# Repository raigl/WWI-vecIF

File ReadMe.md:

# Whirlwind I Vector Graphics Interface

For showing a Whirlwind programme's output, a small hardware
generates vector strokes on X/Y/Z oszilloskopes
and allows to attach light guns.
Guy Fedorkow's WWI simulator ([https://github.com/gfedorkow/Whirlwind-Instruction-Simulator]) running on a Raspberry (B+) 
can drive the interface and run some original WWI programmes.

## Directories

<dl>
<dt> CAD   <dd> 3D Light gun case 3D files 
<dt> DOC   <dd> Documentation (own and collected)  
<dt> KiCad <dd> Schematics and PCB drawings
<dt> src   <dd> Python and Arduino source
</dl>

## Versions

0.3     Working prototype

1.0     Redesigned

## Basics

The interface allows to draw (short) vectors for two channels
on an analog x/y/z display, e.g. an oszilloscope.
Points are drawn as zero-length vectors.

The D/A converter used has an internal reference of 2.048V, 12 bits
resolution and produces 0..2.047V in steps of 1/4096. 
WWI uses 10 bits plus sign, i.e. +/- 1023.
Thus the coordinate unit corresponds to 1mV internally.
The output state amplifies by 3 (and shifts to zero base), 
thus supplies +/- 3V and 3mV per unit. 

Drawing a vector is done by setting two integrators to the start point,
then provide a speed and start the integrators for 50µs,
which at the same time provides a strobe for the z axis.
With maximum speed (-1023 or +1023, i.e. 0 or 2.047V), the movement is 1/8 of the full coordinate range -1.0 .. +1.0,
i.e. 256 coordinate units or 250mV. 
Thus coordinate differences must be multiplied by 4 to set the speed. 
Longer vectors must be drawn as segments.

The display should be setup such that increasing both coordinates
moves the point right and up.

Character display is not done by hardware as in WWI,
but by software as a chain of segments;
this requires a precise setup of the mid voltage
to 1.023V; otherwise the characters are blurred.

Vector drawing was inspried by the Vectrex gaming console.
Original WWI hardware used a more elaborate method:
A fixed ramp generator (for each coordinate) was multiplied by
the vector delta coordinate provided. 
The advantage is that the end points and do not depend on the precision of the integration capacitor.
Also the strobe start and end could be slightly before and after the end of the ramp, 
ensuring that a chain of vectors has no gaps.

## Displays
 
To display the vectors, the display device must have analog inputs for X/Y mode
and a (digital) Z input for intensitiy modulation.

To better mimic the original, the vector interface board provides
a display bus connector to be used with one or more display tap boards,
which are located directly near a display.

Each display tap board has two switches to select one or both intensification
lines (the original had 15). 

A light gun (light pen) for interactive mode can be connected to a display tap board
and configured for one of two light gun inputs.

Four more switches with lamps (LEDs) can be set by either the user or WWI 
programme.

Displays could in particular be oszilloscopes with a trace blanking
or unblanking input (Z-input).
The amplitude of the X and Y signals is &plusmn;3V which can be attenuated
with a potentiometer on the board.
Z output is 5V (TTL) digital output with 50µs active pulses.
Polarity can be configured on the tap board.

Displays that work without modifications are:
- Grundig GO-40Z oszilloscope (with Z-option)
- Tektronix 1740A oszilloscope 
- Tektronix 611 storage display unit

The Tektronix 611 can be swiched to non-storage mode and is normally 
internally wired for +/- 1V sensitivity; 
thus the potentimeters on the tap board are required.

Several other oscilloscopes have a Z option, but often require
at least 20V to blank the trace.
For this cases, a variant of the tap board has provisions for a voltage converter
and corresponding output amplifier.
Some (e.g. Hameg) are designed for blanking small parts of the trace
only by a diode clamp for the coupling capacitor;
this diode has to be removed or reversed, otherwise the blanking would not work.
 
A Hameg HM512 was succesfully modified by reversing the diode and also
adding internally a small amplifier to obtain larger voltage swing
from the Z-input. 

## I²C Bus

The interface board has a connection to access the Rapi's (second) I²C bus,
shifted to 5V operation.

With upto eight PCF8574, each can drive 8 swiches and lamps.

Note that the WWI had no console, but was to a large extend controlled
by panel switches and lights.

## 5V only operation

The board can be driven by a 5V Arduino.
In this case, JP3 must be cut and changed.
The voltage stablizer U9 (LP 2950-3.3) must be used.
The 3.3V pins are then supplied with 5V.

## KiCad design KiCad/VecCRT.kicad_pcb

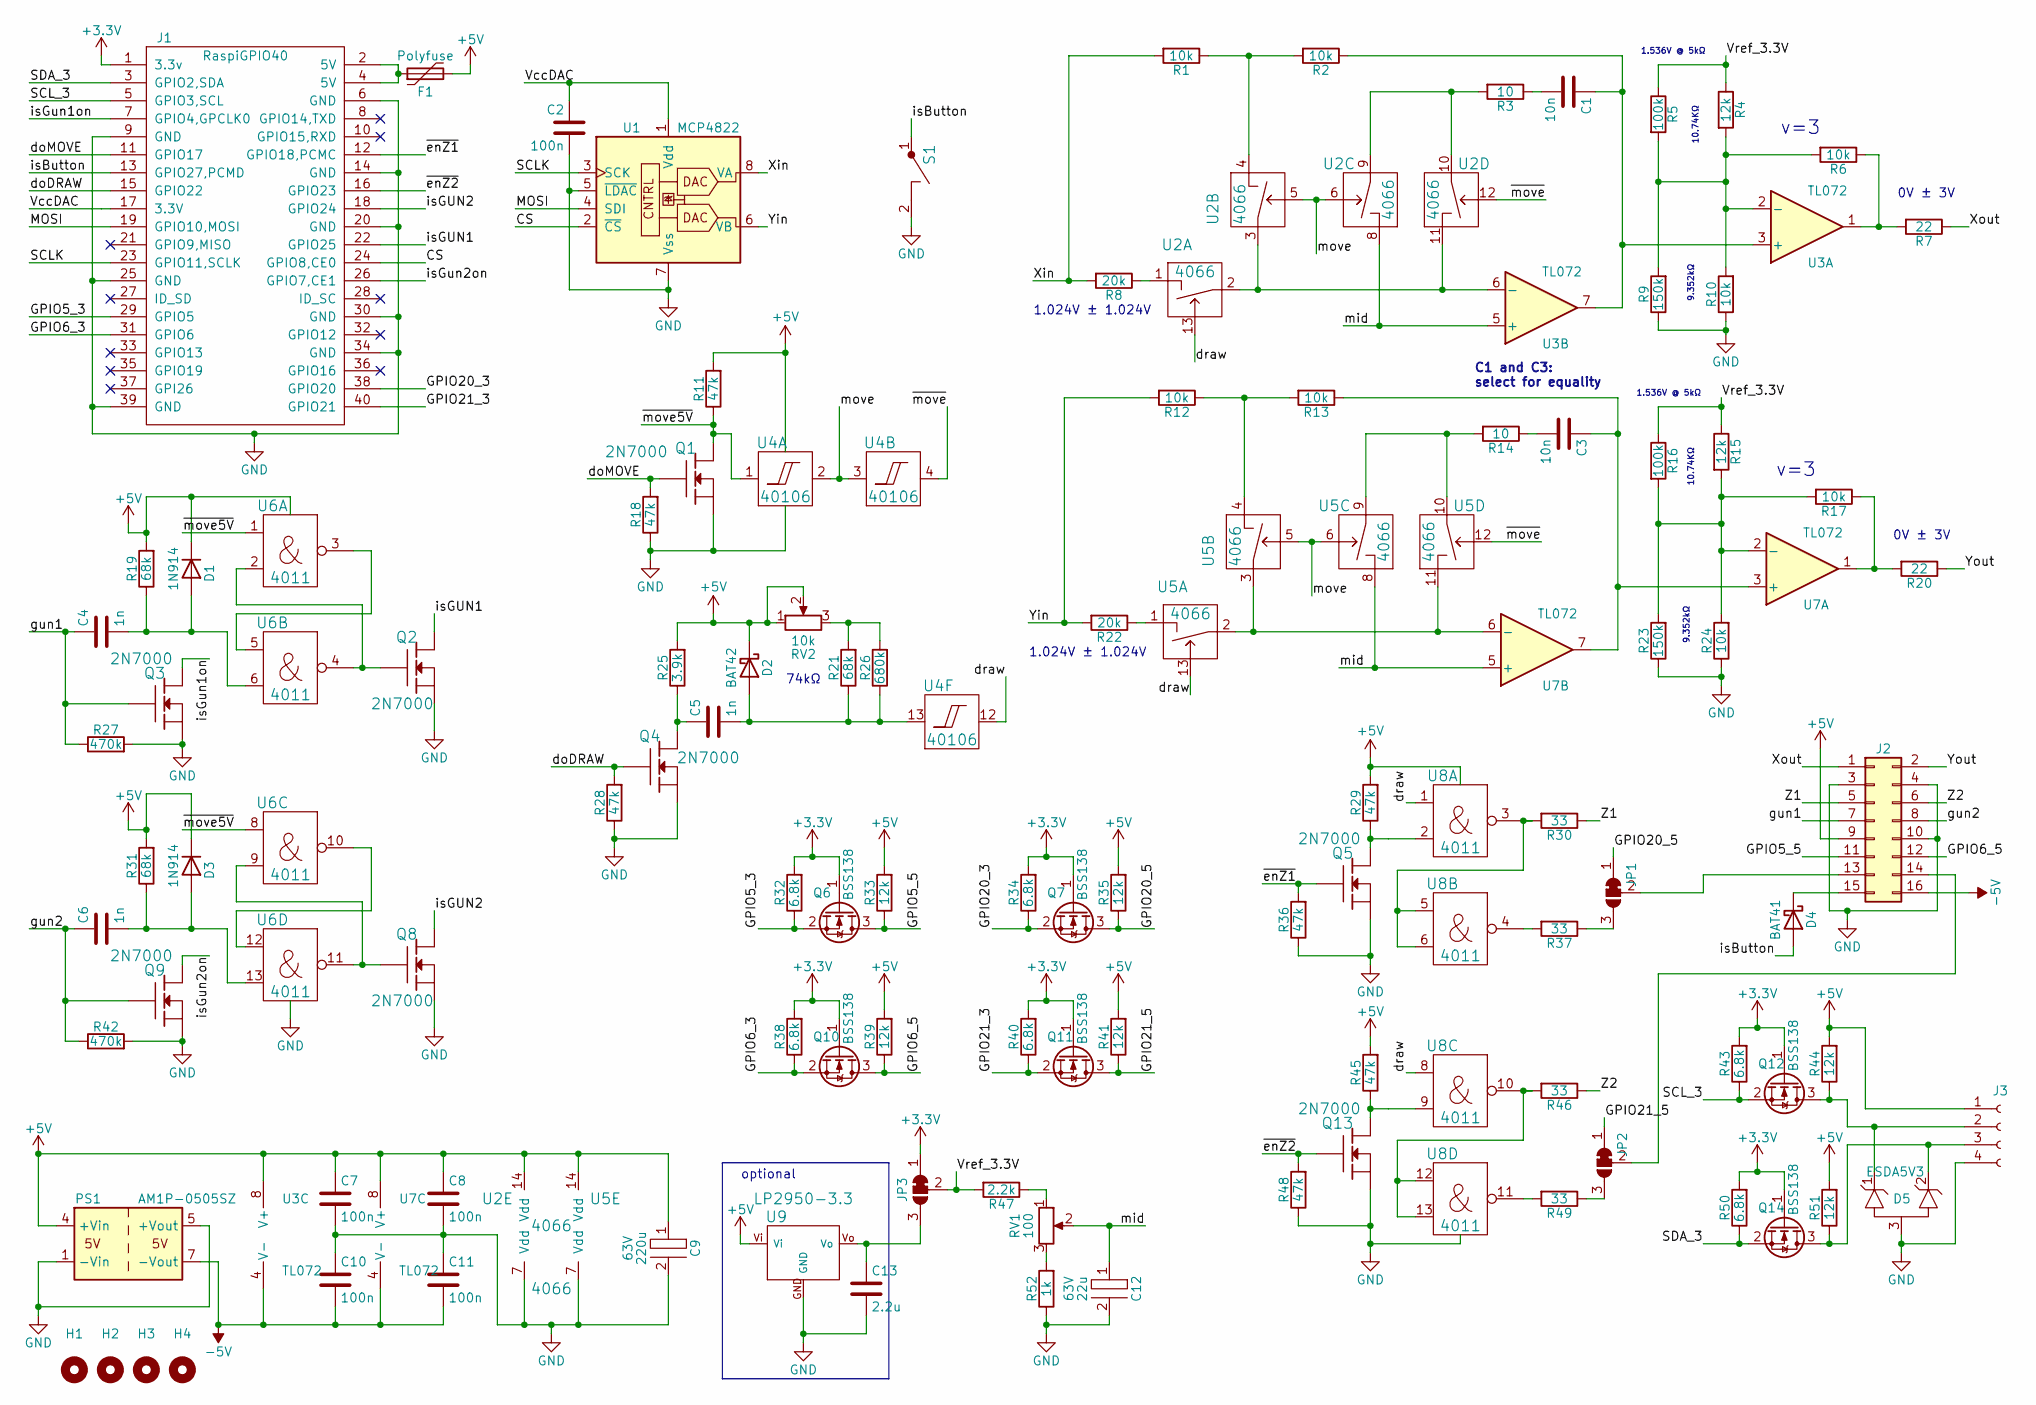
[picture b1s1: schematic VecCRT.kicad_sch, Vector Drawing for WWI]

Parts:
C1, C3: 10n; C2-2
C2, C7, C8, C10, C11: 100n; SM-1206B
C4, C5, C6: 1n; C2-2
C9: 220u; C2-7; Voltage 63V
C12: 22u; C2-7; Voltage 63V
C13: 2.2u; SM-1206B
D1, D3: 1N914; D_DO-35_SOD27_P7.62mm_Horizontal
D2: BAT42; D_DO-35_SOD27_P7.62mm_Horizontal
D4: BAT41; D_DO-35_SOD27_P7.62mm_Horizontal
D5: ESDA5V3; SOT-23_Handsoldering
F1: Polyfuse; Fuse_Bourns_MF-RG300
H1, H2, H3, H4: MountingHole; MountingHole_3.2mm_M3
J1: RaspiGPIO40; Wannenstecker_2x20_V
J2: Conn_02x08_Odd_Even; Wannenstecker_2x08_V
J3: Conn_01x04_Female; PSS_4
JP1, JP2: SolderJumper_3_Open; SolderJumper-3_P1.3mm_Bridged12_RoundedPad1.0x1.5mm
JP3: SolderJumper_3_Bridged12; SolderJumper-3_P1.3mm_Bridged12_RoundedPad1.0x1.5mm
PS1: AM1P-0505SZ; AM1P-SZ
Q1, Q2, Q3, Q4, Q5, Q8, Q9, Q13: 2N7000; FETsgd_inline
Q6, Q7, Q10, Q11, Q12, Q14: BSS138; SOT-23
R1, R2, R6, R10, R12, R13, R17, R24: 10k; R4-2
R3, R14: 10; R4-2
R4, R15: 12k; R4-2
R5, R16: 100k; R4-2
R7, R20: 22; R4-2
R8, R22: 20k; R4-2
R9, R23: 150k; R4-2
R11, R29, R45: 47k; R4-2
R18, R28, R36, R48: 47k; SM-1206B
R19, R21, R31: 68k; R4-2
R25: 3.9k; R4-2
R26: 680k; SM-1206B
R27, R42: 470k; SM-1206B
R30, R37, R46, R49: 33; R4-2
R32, R34, R38, R40, R43, R50: 6.8k; SM-1206B
R33, R35, R39, R41, R44, R51: 12k; SM-1206B
R47: 2.2k; R4-2
R52: 1k; R4-2
RV1: 100; Pot64y
RV2: 10k; Pot64y
S1: TASTER; Tast2mil
U1: MCP4822; DIP-8_300
U2, U5: 4066; DIP-14_W7.62mm_LongPads
U3, U7: TL072; DIP-8_300
U4: 40106; DIP-14_W7.62mm_LongPads
U6, U8: 4011; DIP-14_W7.62mm_LongPads
U9: LP2950-3.3; TO-92ViGNDVo

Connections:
+3.3V: J1.1 (3.3v), JP3.1 (A), Q6.1 (G), Q7.1 (G), Q10.1 (G), Q11.1 (G), Q12.1 (G), Q14.1 (G), R32.2, R34.2, R38.2, R40.2, R43.2, R50.2
+5V: C7.1, C8.1, C9.1, D1.1 (K), D2.1 (K), D3.1 (K), F1.2, J2.9, J3.1, PS1.4 (+Vin), R11.2, R19.2, R25.2, R29.2, R31.2, R33.2, R35.2, R39.2, R41.2, R44.2, R45.2, R51.2, RV2.1, RV2.2, U2.14 (Vdd), U3.8 (V+), U4.14, U5.14 (Vdd), U6.14 (VDD), U7.8 (V+), U8.14 (VDD), U9.Vi
-5V: C10.2, C11.2, J2.16, PS1.7 (-Vout), U3.4 (V-), U7.4 (V-)
/CS: J1.24 (GPIO8,CE0), U1.2 (~CS)
/GPIO5_3: J1.29 (GPIO5), Q6.2 (S), R32.1
/GPIO5_5: J2.11, Q6.3 (D), R33.1
/GPIO6_3: J1.31 (GPIO6), Q10.2 (S), R38.1
/GPIO6_5: J2.12, Q10.3 (D), R39.1
/GPIO20_3: J1.38 (GPIO20), Q7.2 (S), R34.1
/GPIO20_5: JP1.1 (A), Q7.3 (D), R35.1
/GPIO21_3: J1.40 (GPIO21), Q11.2 (S), R40.1
/GPIO21_5: JP2.1 (A), Q11.3 (D), R41.1
/MOSI: J1.19 (GPIO10,MOSI), U1.4 (SDI)
/SCLK: J1.23 (GPIO11,SCLK), U1.3 (SCK)
/SCL_3: J1.5 (GPIO3,SCL), Q12.2 (S), R43.1
/SDA_3: J1.3 (GPIO2,SDA), Q14.2 (S), R50.1
/VccDAC: C2.1, J1.17 (3.3V), U1.1 (Vdd)
/Vref_3.3V: JP3.2 (C), R4.1, R5.1, R15.1, R16.1, R47.2
/Xin: R1.2, R8.2, U1.8 (VA)
/Xout: J2.1, R7.1
/Yin: R12.2, R22.2, U1.6 (VB)
/Yout: J2.2, R20.1
/Z1: J2.5, R30.1
/Z2: J2.6, R46.1
/doDRAW: J1.15 (GPIO22), Q4.G, R28.2
/doMOVE: J1.11 (GPIO17), Q1.G, R18.2
/draw: U2.13, U4.12, U5.13, U8.1, U8.8
/gun1: C4.1, J2.7, Q3.G, R27.1
/gun2: C6.1, J2.8, Q9.G, R42.1
/isButton: D4.2 (A), J1.13 (GPIO27,PCMD), S1.1
/isGUN1: J1.22 (GPIO25), Q2.D
/isGUN2: J1.18 (GPIO24), Q8.D
/isGun1on: J1.7 (GPIO4,GPCLK0), Q3.D
/isGun2on: J1.26 (GPIO7,CE1), Q9.D
/mid: C12.1, RV1.2, U2.8, U3.5 (+), U5.8, U7.5 (+)
/move: U2.5, U2.6, U4.2, U4.3, U5.5, U5.6
/~enZ1: J1.12 (GPIO18,PCMC), Q5.G, R36.2
/~enZ2: J1.16 (GPIO23), Q13.G, R48.2
/~move5V: Q1.D, R11.1, U4.1, U6.1, U6.8
/~move: U2.12, U4.4, U5.12
GND: C2.2, C7.2, C8.2, C9.2, C10.1, C11.1, C12.2, C13.2, D5.3 (A), J1.6 (GND), J1.9 (GND), J1.14 (GND), J1.20 (GND), J1.25 (GND), J1.30 (GND), J1.34 (GND), J1.39 (GND), J2.3, J2.4, J2.10, J3.4, PS1.1 (-Vin), PS1.5 (+Vout), Q1.S, Q2.S, Q3.S, Q4.S, Q5.S, Q8.S, Q9.S, Q13.S, R9.1, R10.1, R18.1, R23.1, R24.1, R27.2, R28.1, R36.1, R42.2, R48.1, R52.1, S1.2, U1.5 (~LDAC), U1.7 (Vss), U2.7 (Vdd), U4.7 (e), U5.7 (Vdd), U6.7 (VSS), U8.7 (VSS), U9.GND
unnamed: C1.1, R2.1, U3.3 (+), U3.7
unnamed: C1.2, R3.1
unnamed: C3.1, R13.1, U7.3 (+), U7.7
unnamed: C3.2, R14.1
unnamed: C4.2, D1.2 (A), R19.1, U6.6
unnamed: C5.1, Q4.D, R25.1
unnamed: C5.2, D2.2 (A), R21.1, R26.1, U4.13
unnamed: C6.2, D3.2 (A), R31.1, U6.13
unnamed: C13.1, JP3.3 (B), U9.Vo
unnamed: D4.1 (K), J2.15
unnamed: D5.1 (K1), J3.2, Q12.3 (D), R44.1
unnamed: D5.2 (K2), J3.3, Q14.3 (D), R51.1
unnamed: F1.1, J1.2 (5V), J1.4 (5V)
unnamed: J2.13, JP1.2 (C)
unnamed: J2.14, JP2.2 (C)
unnamed: JP1.3 (B), R37.1
unnamed: JP2.3 (B), R49.1
unnamed: Q2.G, U6.2, U6.4
unnamed: Q5.D, R29.1, U8.2
unnamed: Q8.G, U6.9, U6.11
unnamed: Q13.D, R45.1, U8.9
unnamed: R1.1, R2.2, U2.4
unnamed: R3.2, U2.9, U2.10
unnamed: R6.1, R7.2, U3.1
unnamed: R8.1, U2.1
unnamed: R4.2, R5.2, R6.2, R9.2, R10.2, U3.2 (-)
unnamed: R12.1, R13.2, U5.4
unnamed: R14.2, U5.9, U5.10
unnamed: R15.2, R16.2, R17.2, R23.2, R24.2, U7.2 (-)
unnamed: R17.1, R20.2, U7.1
unnamed: R21.2, R26.2, RV2.3
unnamed: R22.1, U5.1
unnamed: R30.2, U8.3, U8.5, U8.6
unnamed: R37.2, U8.4
unnamed: R46.2, U8.10, U8.12, U8.13
unnamed: R47.1, RV1.1
unnamed: R49.2, U8.11
unnamed: R52.2, RV1.3
unnamed: U2.2, U2.3, U2.11, U3.6 (-)
unnamed: U5.2, U5.3, U5.11, U7.6 (-)
unnamed: U6.3, U6.5
unnamed: U6.10, U6.12

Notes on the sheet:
0V ± 3V
74kΩ
v=3
10.74KΩ
9.352kΩ
1.536V @ 5kΩ
1.024V ± 1.024V
C1 and C3: select for equality
optional

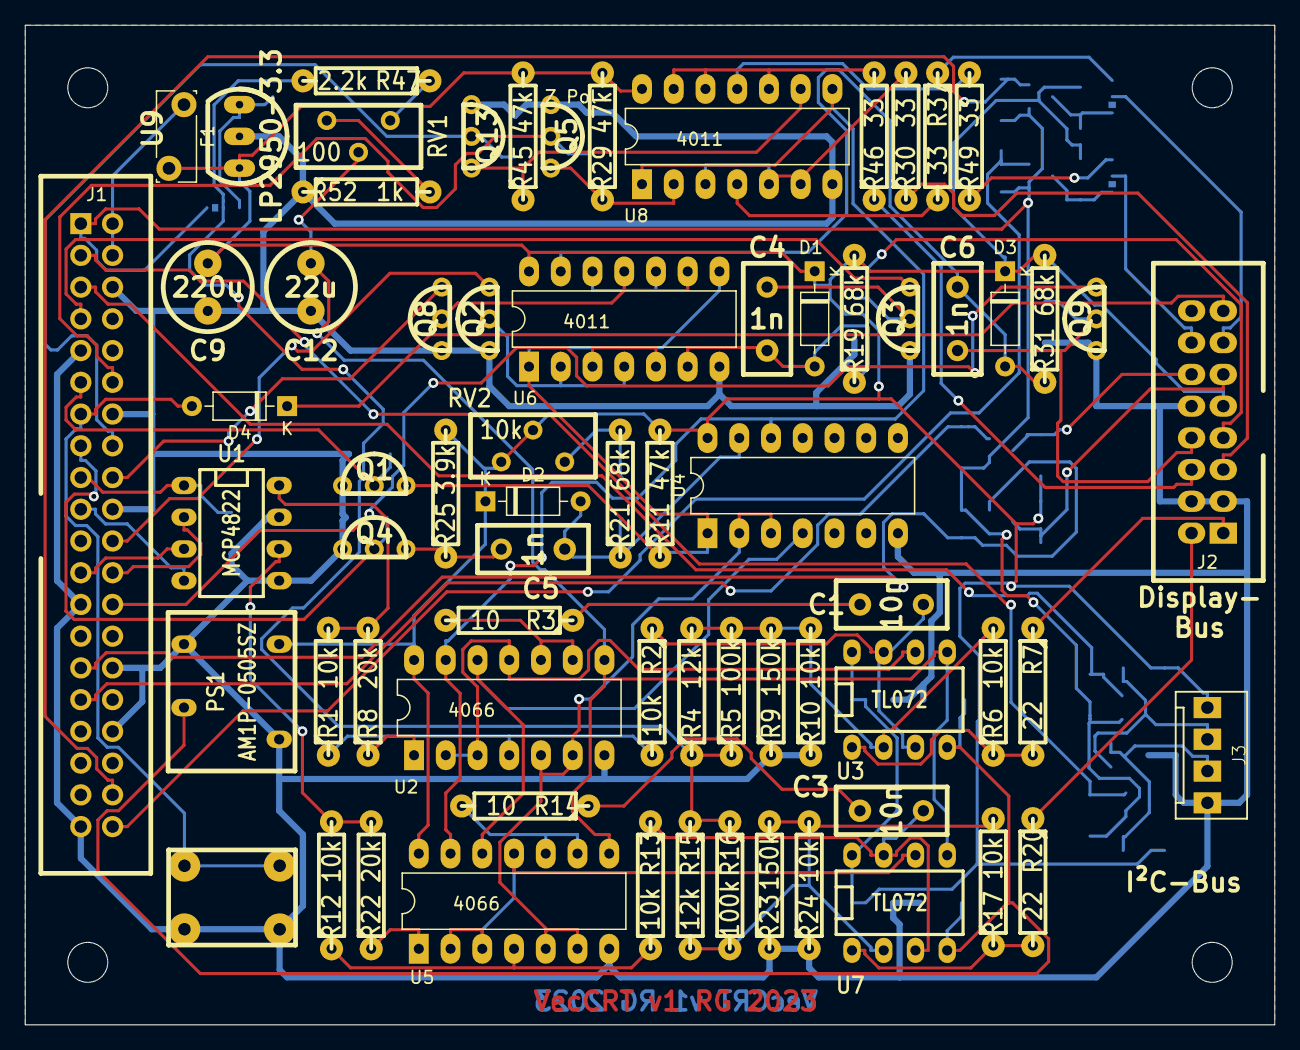
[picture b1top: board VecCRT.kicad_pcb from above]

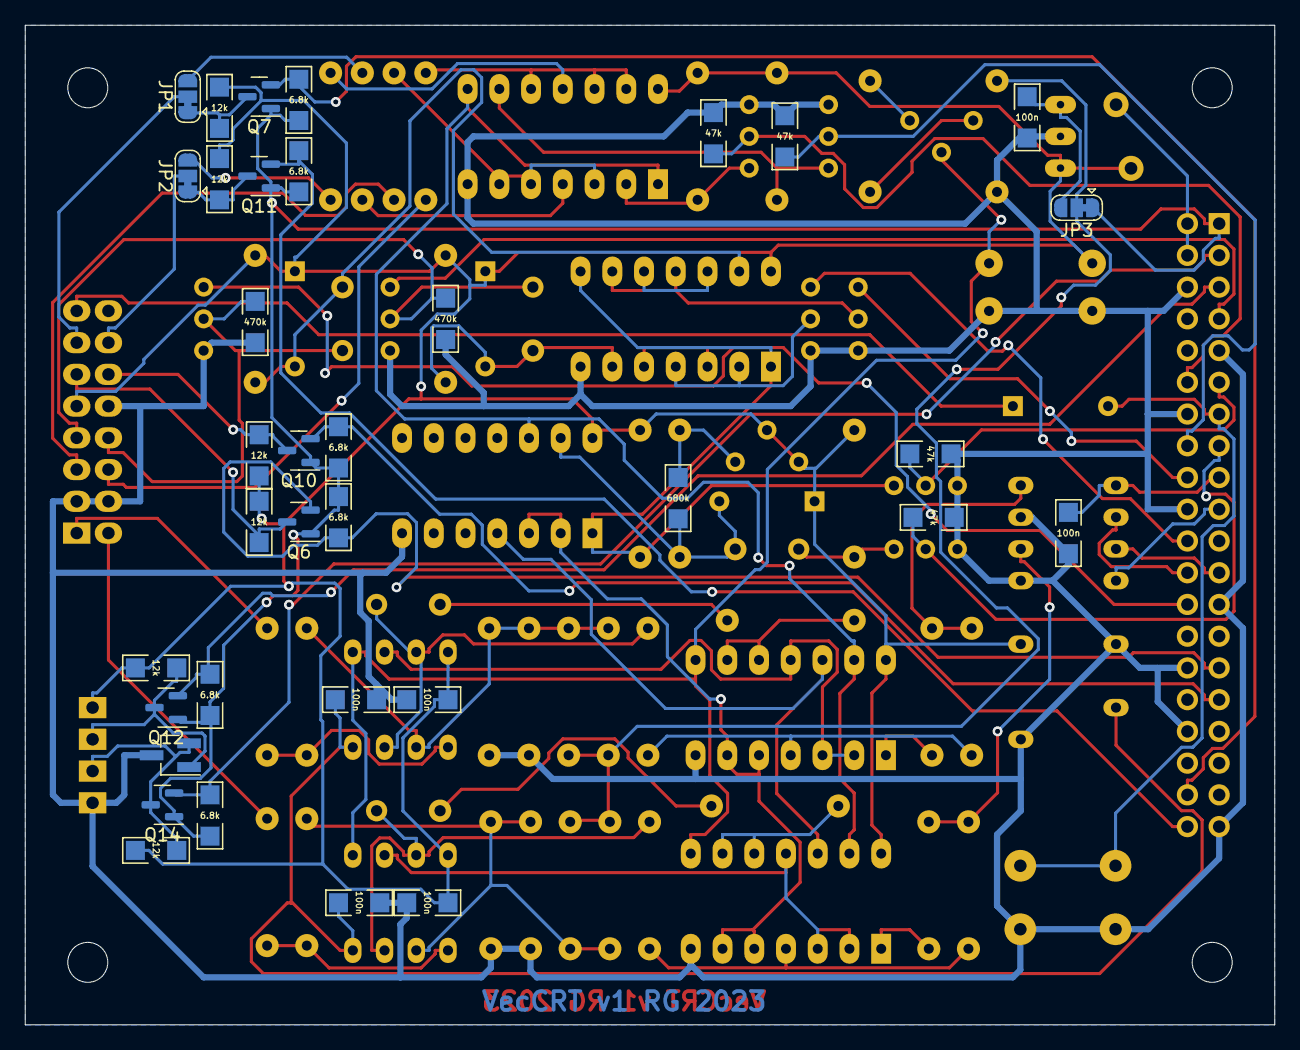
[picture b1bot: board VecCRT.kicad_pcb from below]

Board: 2 copper layers, 100.0 x 80.0 mm, 108 parts (10 on the bottom side), 83 nets.

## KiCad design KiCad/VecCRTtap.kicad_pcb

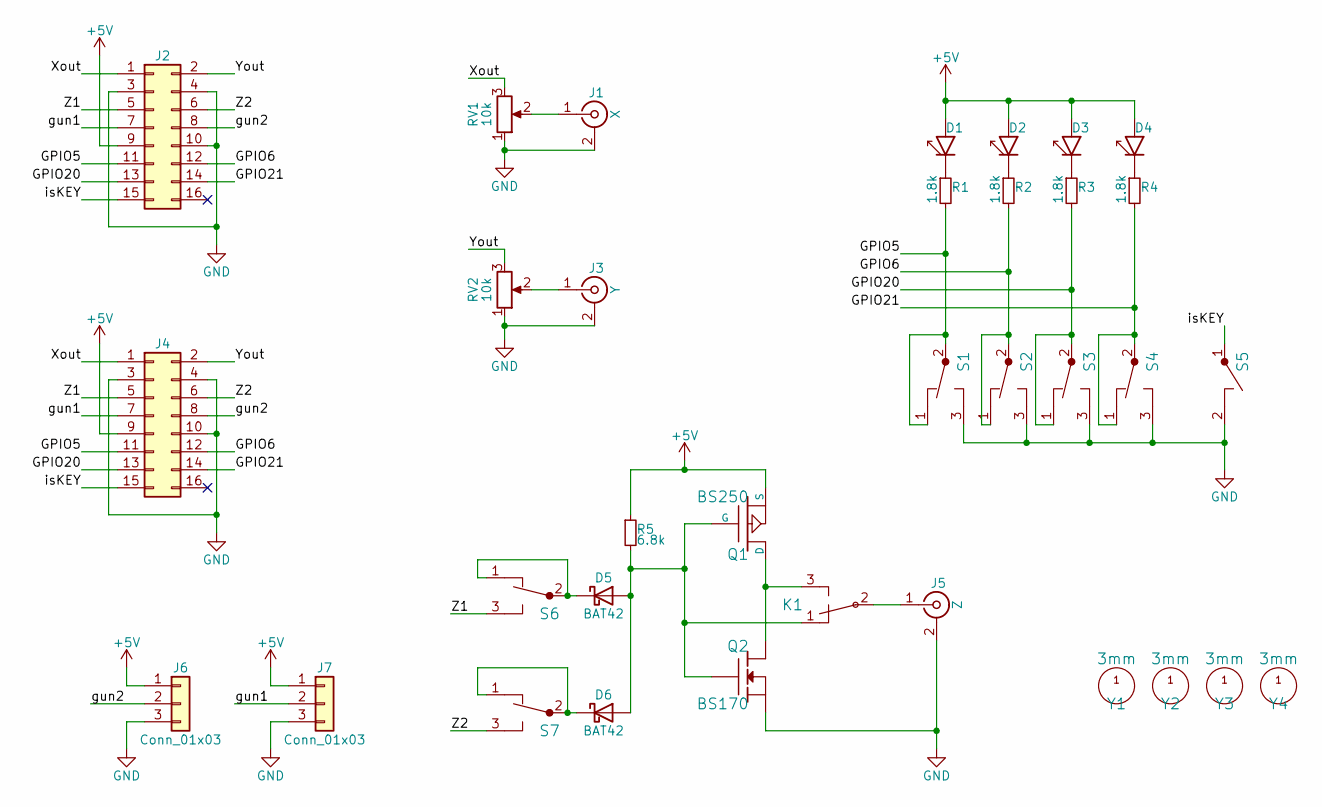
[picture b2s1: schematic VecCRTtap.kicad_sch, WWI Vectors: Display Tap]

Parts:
D1, D2, D3, D4: LED; LED_D5.0mm
D5, D6: BAT42; D3
J1: X; Cinch_liegend
J2, J4: Conn_02x08_Odd_Even; Wannenstecker_2x08_V
J3: Y; Cinch_liegend
J5: Z; Cinch_liegend
J6, J7: Conn_01x03; PSS_3W
K1: 1UM; Pins_3
Q1: BS250; FETdgs_inline
Q2: BS170; FETdgs_inline
R1, R2, R3, R4: 1.8k; R4-2
R5: 6.8k; R4-2
RV1, RV2: 10k; ACP-CA9V10-Trimmer
S1, S2, S3, S4, S6, S7: TASTERU; Sw-T101-Um
S5: TASTER; SW_MEC_5GTH9
Y1, Y2, Y3, Y4: 3mm; Bohrloch3mm

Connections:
+5V: D1.A, D2.A, D3.A, D4.A, J2.9, J4.9, J6.1, J7.1, Q1.S, R5.1
/GPIO5: J2.11, J4.11, R1.2, S1.1, S1.2
/GPIO6: J2.12, J4.12, R2.2, S2.1, S2.2
/GPIO20: J2.13, J4.13, R3.2, S3.1, S3.2
/GPIO21: J2.14, J4.14, R4.2, S4.1, S4.2
/Xout: J2.1, J4.1, RV1.3
/Yout: J2.2, J4.2, RV2.3
/Z1: J2.5, J4.5, S6.3
/Z2: J2.6, J4.6, S7.3
/gun1: J2.7, J4.7, J7.2
/gun2: J2.8, J4.8, J6.2
/isKEY: J2.15, J4.15, S5.1
GND: J1.2 (Ext), J2.3, J2.4, J2.10, J3.2 (Ext), J4.3, J4.4, J4.10, J5.2 (Ext), J6.3, J7.3, Q2.S, RV1.1, RV2.1, S1.3, S2.3, S3.3, S4.3, S5.2
unnamed: D1.K, R1.1
unnamed: D2.K, R2.1
unnamed: D3.K, R3.1
unnamed: D4.K, R4.1
unnamed: D5.1 (K), S6.1, S6.2
unnamed: D5.2 (A), D6.2 (A), K1.1, Q1.G, Q2.G, R5.2
unnamed: D6.1 (K), S7.1, S7.2
unnamed: J1.1 (In), RV1.2
unnamed: J3.1 (In), RV2.2
unnamed: J5.1 (In), K1.2
unnamed: K1.3, Q1.D, Q2.D

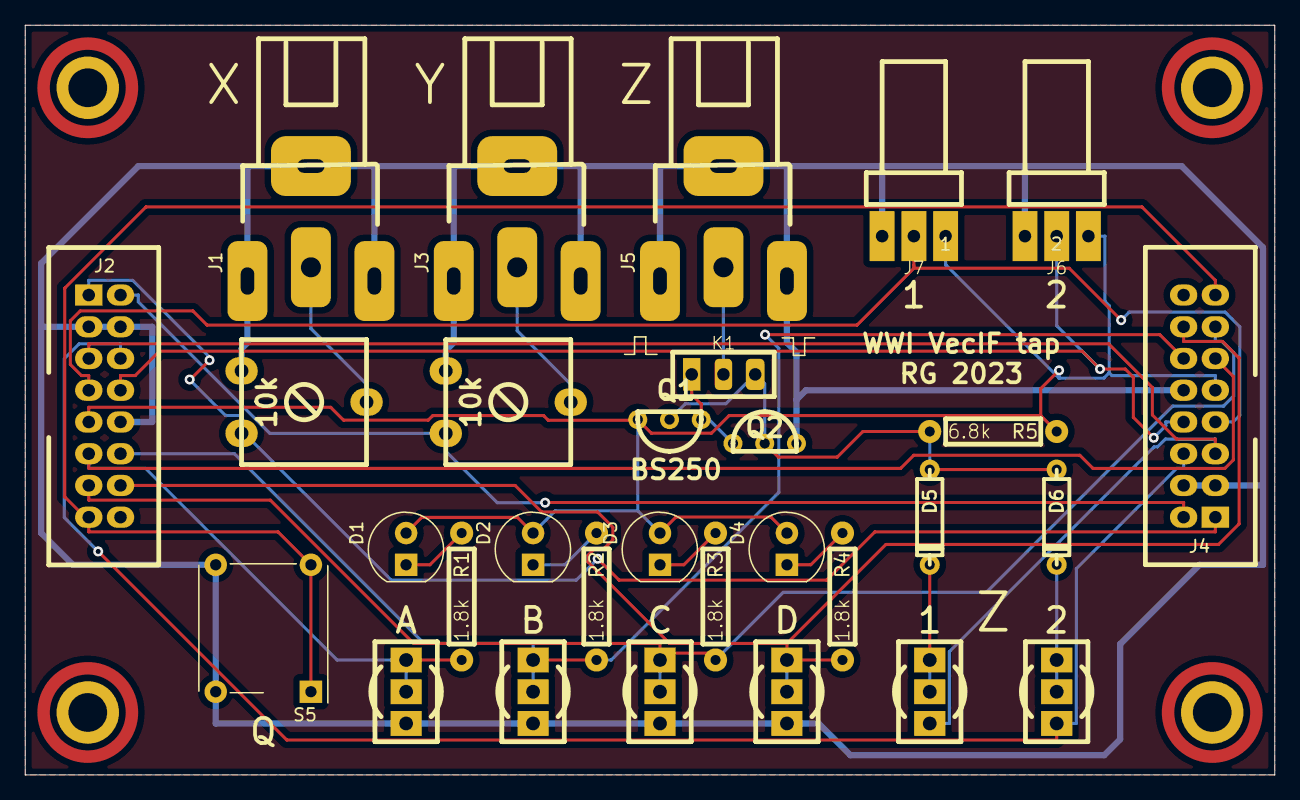
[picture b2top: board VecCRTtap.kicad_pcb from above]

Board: 2 copper layers, 100.0 x 60.0 mm, 34 parts (0 on the bottom side), 24 nets.

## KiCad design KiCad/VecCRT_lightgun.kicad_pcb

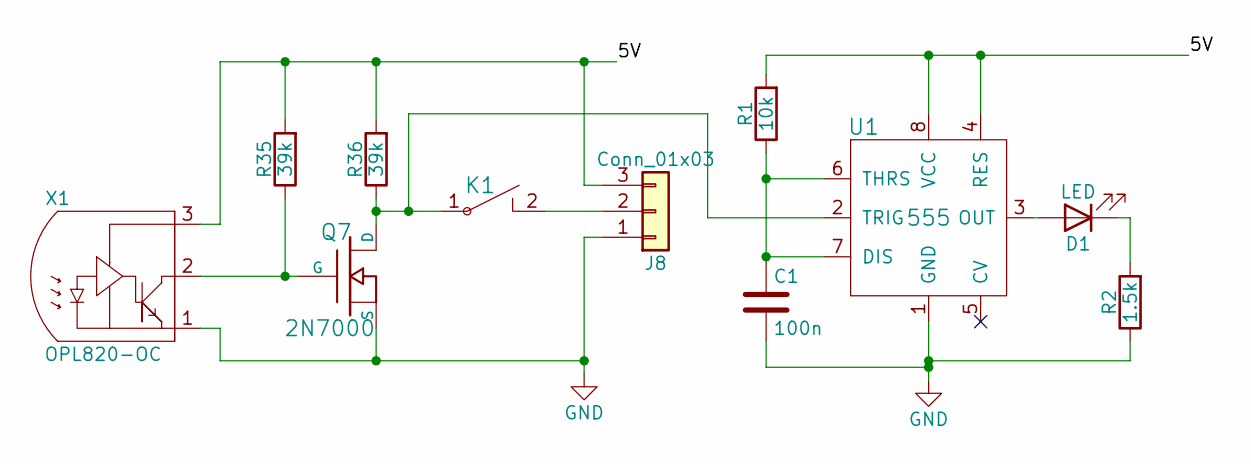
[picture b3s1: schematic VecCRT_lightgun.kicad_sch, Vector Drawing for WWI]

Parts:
C1: 100n; C2-2
D1: LED; Pins_2
J8: Conn_01x03; Pins_3
K1: SchEin; Pins_2
Q7: 2N7000; FETsgd_inline
R1: 10k; R4-2
R2: 1.5k; R4-2
R35, R36: 39k; R4-2
U1: 555; DIP-8_300
X1: OPL820-OC; Pins_3

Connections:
/5V: J8.3, R1.2, R35.2, R36.2, U1.4 (RES), U1.8 (VCC), X1.3
GND: C1.2, J8.1, Q7.S, R2.1, U1.1 (GND), X1.1
unnamed: C1.1, R1.1, U1.6 (THRS), U1.7 (DIS)
unnamed: D1.1 (K), R2.2
unnamed: D1.2 (A), U1.3 (OUT)
unnamed: J8.2, K1.2
unnamed: K1.1, Q7.D, R36.1, U1.2 (TRIG)
unnamed: Q7.G, R35.1, X1.2

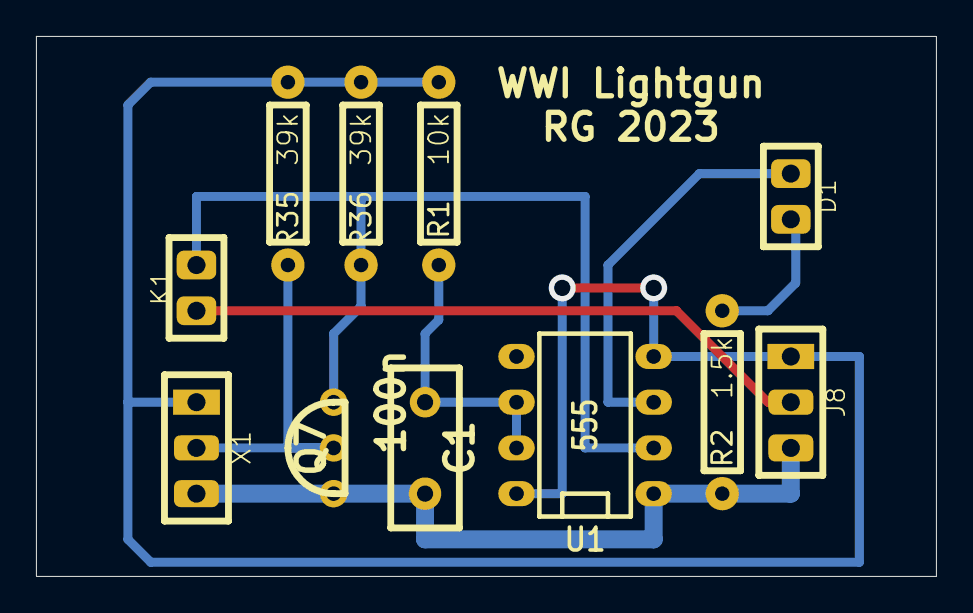
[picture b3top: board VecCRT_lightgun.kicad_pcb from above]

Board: 2 copper layers, 50.0 x 30.0 mm, 11 parts (0 on the bottom side), 8 nets.

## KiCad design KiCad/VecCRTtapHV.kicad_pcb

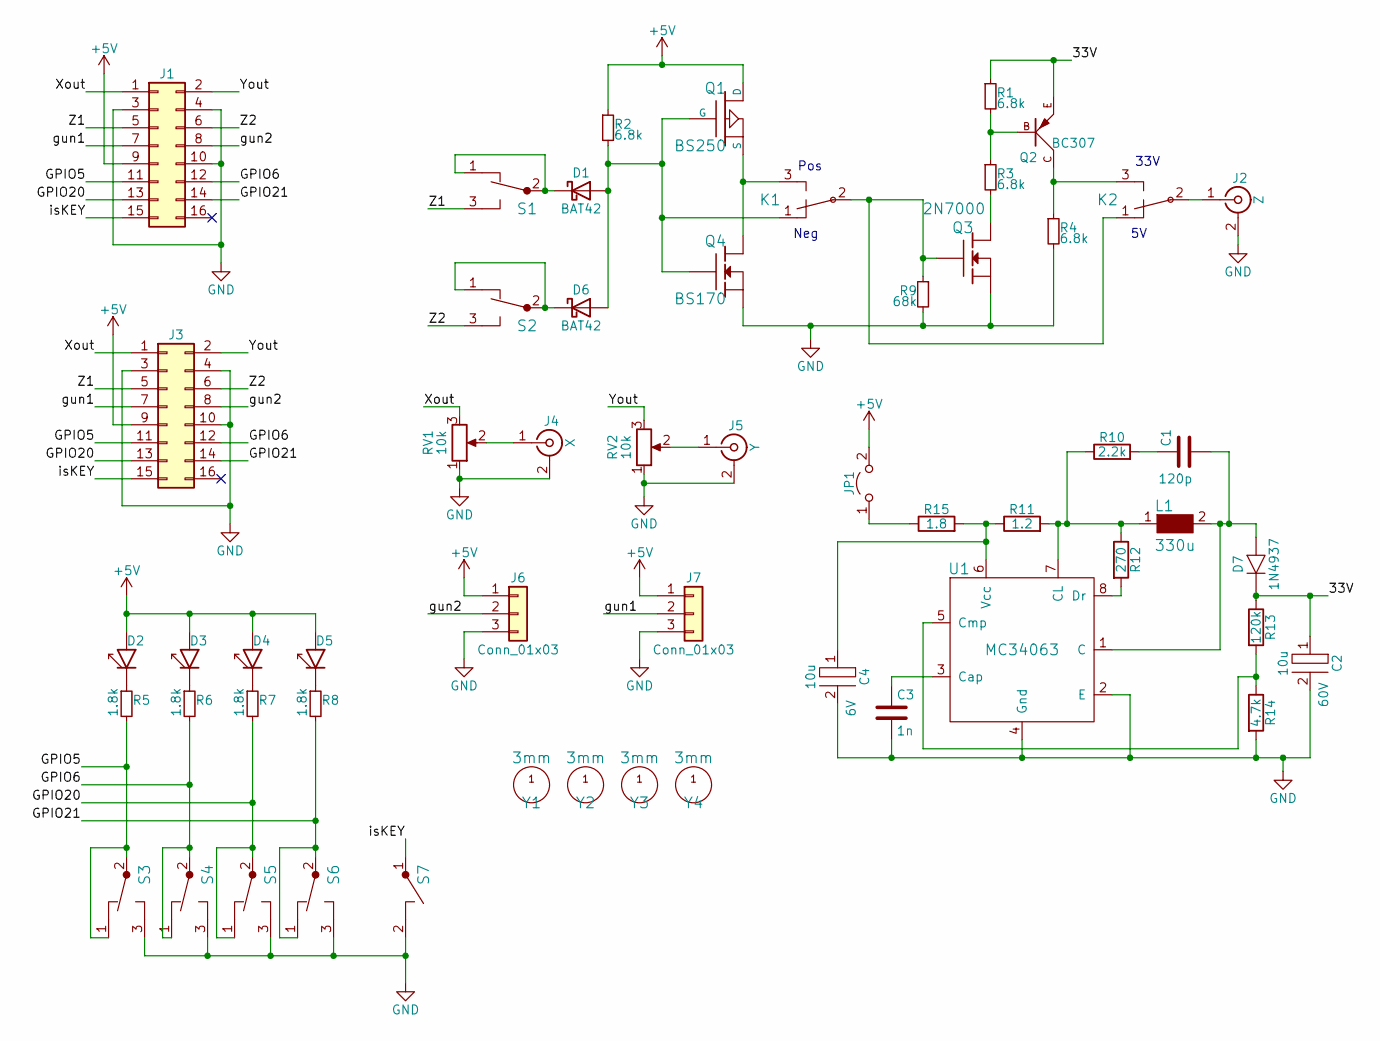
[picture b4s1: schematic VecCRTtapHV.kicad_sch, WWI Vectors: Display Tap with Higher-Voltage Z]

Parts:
C1: 120p; C2-2
C2: 10u; C2-7; Voltage 60V
C3: 1n; C2-2
C4: 10u; C2-7; Voltage 6V
D1, D6: BAT42; D3
D2, D3, D4, D5: LED; LED_D5.0mm
D7: 1N4937; D_DO-35_SOD27_P7.62mm_Horizontal
J1, J3: Conn_02x08_Odd_Even; Wannenstecker_2x08_V
J2: Z; Cinch_liegend
J4: X; Cinch_liegend
J5: Y; Cinch_liegend
J6, J7: Conn_01x03; PSS_3
JP1: Jumper_2_Open; Pins_2
K1, K2: 1UM; Pins_3
L1: 330u; C2-7
Q1: BS250; FETsgd_inline
Q2: BC307; TO-92_RG_EBC
Q3: 2N7000; FETsgd_inline
Q4: BS170; FETsgd_inline
R1, R2, R3, R4: 6.8k; R4-2
R5, R6, R7, R8: 1.8k; R4-2
R9: 68k; R4-2
R10: 2.2k; R4-2
R11: 1.2; R4-2
R12: 270; R4-2
R13: 120k; R4-2
R14: 4.7k; R4-2
R15: 1.8; R4-2
RV1, RV2: 10k; ACP-CA9V10-Trimmer
S1, S2, S3, S4, S5, S6: TASTERU; Sw-T101-Um
S7: TASTER; SW_MEC_5GTH9
U1: MC34063; DIP-8_300
Y1, Y2, Y3, Y4: 3mm; Bohrloch3mm

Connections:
+5V: D2.A, D3.A, D4.A, D5.A, J1.9, J3.9, J6.1, J7.1, JP1.2 (B), Q1.D, R2.1
/33V: C2.1, D7.1 (K), Q2.E, R1.1, R13.1
/GPIO5: J1.11, J3.11, R5.2, S3.1, S3.2
/GPIO6: J1.12, J3.12, R6.2, S4.1, S4.2
/GPIO20: J1.13, J3.13, R7.2, S5.1, S5.2
/GPIO21: J1.14, J3.14, R8.2, S6.1, S6.2
/Xout: J1.1, J3.1, RV1.3
/Yout: J1.2, J3.2, RV2.3
/Z1: J1.5, J3.5, S1.3
/Z2: J1.6, J3.6, S2.3
/gun1: J1.7, J3.7, J7.2
/gun2: J1.8, J3.8, J6.2
/isKEY: J1.15, J3.15, S7.1
GND: C2.2, C3.2, C4.2, J1.3, J1.4, J1.10, J2.2 (Ext), J3.3, J3.4, J3.10, J4.2 (Ext), J5.2 (Ext), J6.3, J7.3, Q3.S, Q4.S, R4.2, R9.2, R14.2, RV1.1, RV2.1, S3.3, S4.3, S5.3, S6.3, S7.2, U1.2 (E), U1.4 (Gnd)
unnamed: C1.1, R10.2
unnamed: C1.2, D7.2 (A), L1.2, U1.1 (C)
unnamed: C3.1, U1.3 (Cap)
unnamed: C4.1, R11.1, R15.2, U1.6 (Vcc)
unnamed: D1.1 (K), S1.1, S1.2
unnamed: D1.2 (A), D6.2 (A), K1.1, Q1.G, Q4.G, R2.2
unnamed: D2.K, R5.1
unnamed: D3.K, R6.1
unnamed: D4.K, R7.1
unnamed: D5.K, R8.1
unnamed: D6.1 (K), S2.1, S2.2
unnamed: J2.1 (In), K2.2
unnamed: J4.1 (In), RV1.2
unnamed: J5.1 (In), RV2.2
unnamed: JP1.1 (A), R15.1
unnamed: K1.2, K2.1, Q3.G, R9.1
unnamed: K1.3, Q1.S, Q4.D
unnamed: K2.3, Q2.C, R4.1
unnamed: L1.1, R10.1, R11.2, R12.1, U1.7 (CL)
unnamed: Q2.B, R1.2, R3.1
unnamed: Q3.D, R3.2
unnamed: R12.2, U1.8 (Dr)
unnamed: R13.2, R14.1, U1.5 (Cmp)

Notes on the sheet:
Pos
33V
Neg

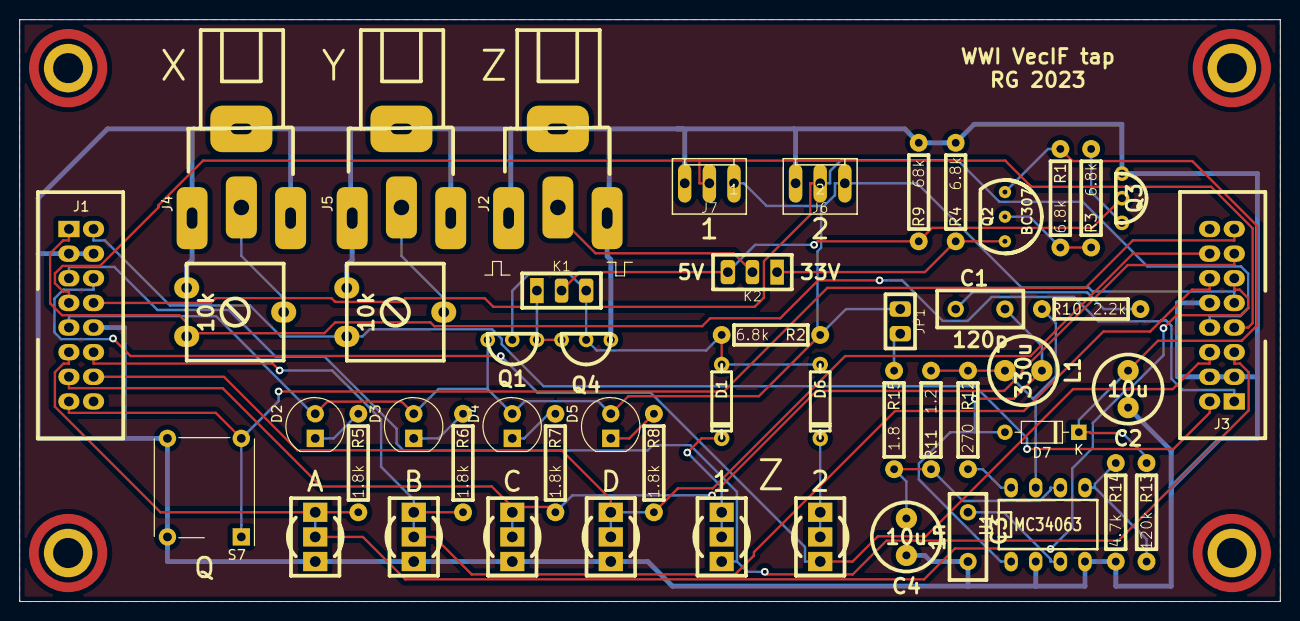
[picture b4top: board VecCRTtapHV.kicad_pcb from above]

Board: 2 copper layers, 130.0 x 60.0 mm, 55 parts (0 on the bottom side), 37 nets.

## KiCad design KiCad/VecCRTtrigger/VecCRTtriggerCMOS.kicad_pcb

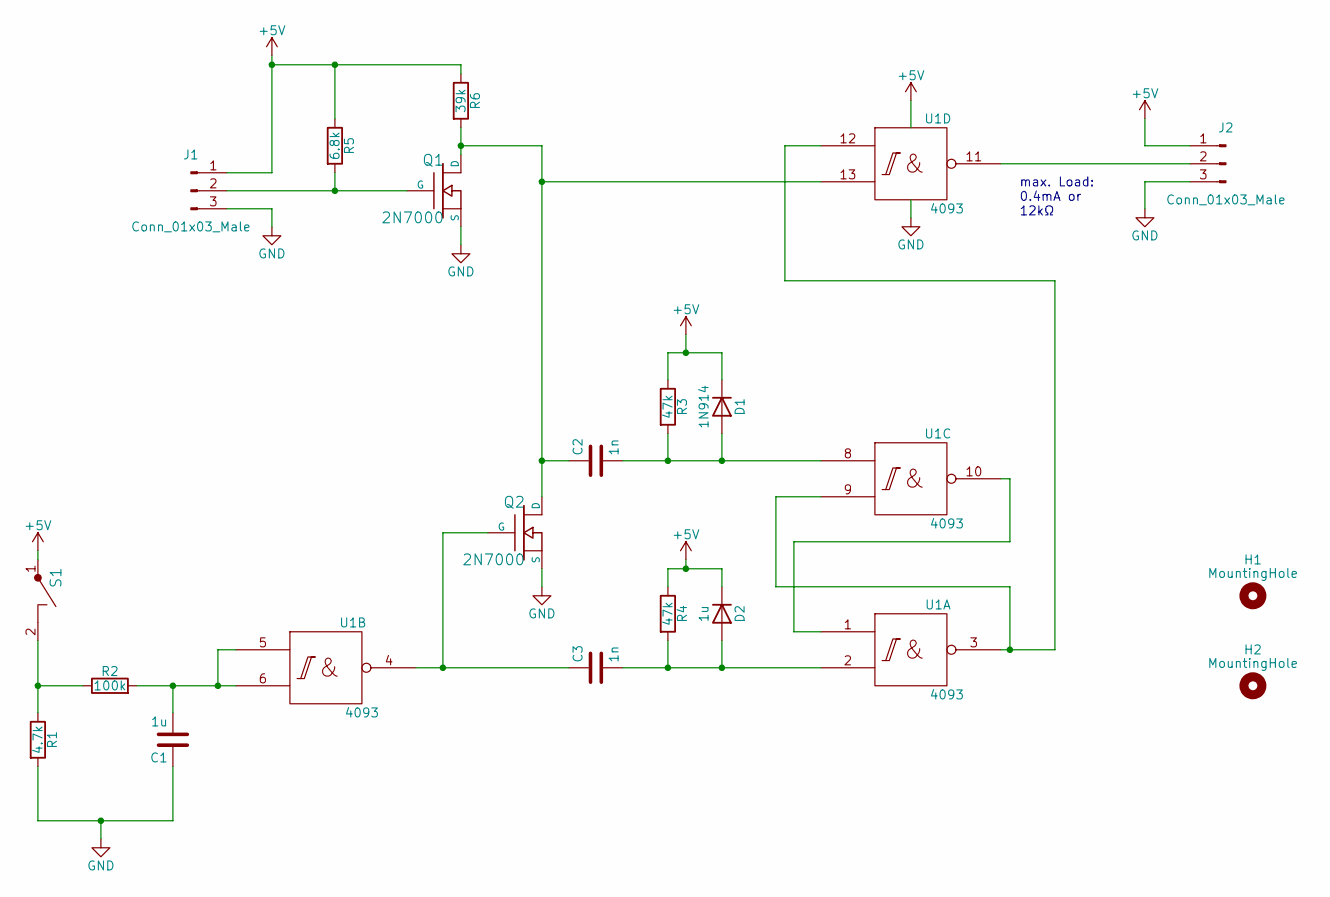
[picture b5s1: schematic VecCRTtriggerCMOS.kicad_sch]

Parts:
C1: 1u; C2-2_liegend
C2, C3: 1n; C2-2
D1: 1N914; D3
D2: 1u; D3
H1, H2: MountingHole; MountingHole_2.5mm
J1, J2: Conn_01x03_Male; Pins_3
Q1, Q2: 2N7000; FETsgd_inline
R1: 4.7k; R4-2
R2: 100k; R4-2
R3, R4: 47k; R4-2
R5: 6.8k; R4-2
R6: 39k; R4-2
S1: TASTER; Pins_2
U1: 4093; DIP-14_W7.62mm_LongPads

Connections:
+5V: D1.1 (K), D2.1 (K), J1.1, J2.1, R3.1, R4.1, R5.1, R6.1, S1.1, U1.14 (Vdd)
GND: C1.1, J1.3, J2.3, Q1.S, Q2.S, R1.2, U1.7 (Vss)
unnamed: C1.2, R2.2, U1.5, U1.6
unnamed: C2.1, Q1.D, Q2.D, R6.2, U1.13
unnamed: C2.2, D1.2 (A), R3.2, U1.8
unnamed: C3.2, D2.2 (A), R4.2, U1.2
unnamed: J1.2, Q1.G, R5.2
unnamed: J2.2, U1.11
unnamed: R1.1, R2.1, S1.2
unnamed: U1.3, U1.9, U1.12
unnamed: C3.1, Q2.G, U1.4
unnamed: U1.1, U1.10

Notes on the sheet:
max. Load: 0.4mA or 12kΩ

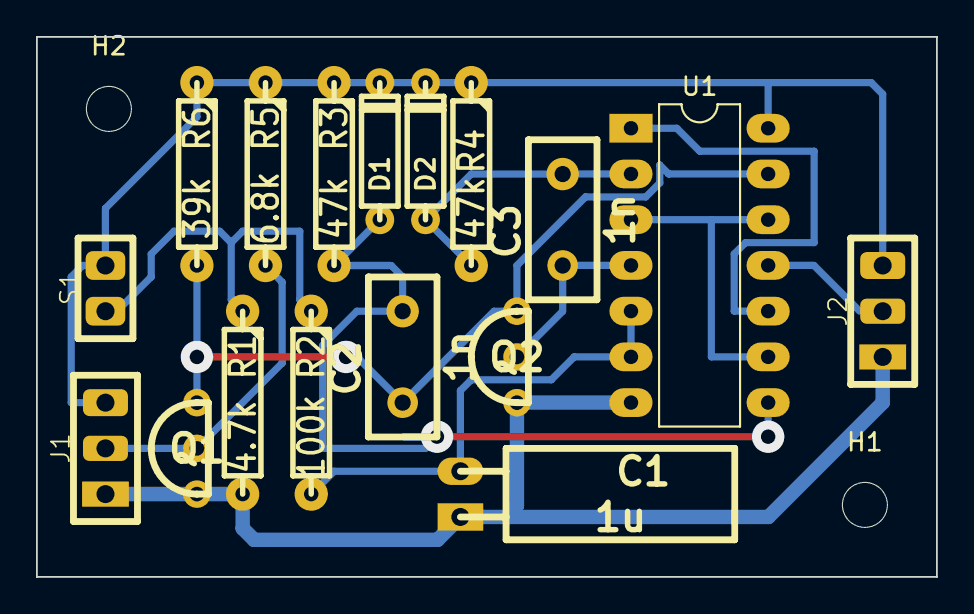
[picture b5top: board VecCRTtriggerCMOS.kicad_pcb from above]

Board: 2 copper layers, 50.0 x 30.0 mm, 19 parts (0 on the bottom side), 12 nets.

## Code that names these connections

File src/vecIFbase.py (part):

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hold_delay = 10   # .0E-6     # one-shot recovery time
 
# pin definitions in BCM numbering
pin_doMove = 17
pin_doDraw = 22
pin_enZ1 = 18
pin_enZ2 = 23
pin_isKey = 27
pin_isGun1 = 25
pin_isGun2 = 24
pin_isGun1on = 4
pin_isGun2on = 7
pin_LED1 = 5
pin_LED2 = 6
pin_LED3 = 20
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    # move to destination
    setDA(0, posx)
    setDA(1, posy)
    gpio.output(pin_doMove, 1)
    delay_us(move_delay)
    gpio.output(pin_doMove, 0)
                        
def drawSegment(speedx, speedy):		
    # set speed
    setDA(0, speedx)
    setDA(1, speedy)
    gpio.output(pin_doDraw, 1)
    delay_us(draw_delay)
    gpio.output(pin_doDraw, 0)
    
def setOutLine(line):
    """ Enables or disbles output lines
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        i.e. 0 for none, 1 for 1, 2 for 2 and 3 for both
    """
    if line == 1 or line == 3:
        gpio.output(pin_enZ1, 0)  # inverted: 0 is enable, 1 is disable
    else:
        gpio.output(pin_enZ1, 1)  
    if line == 2 or line == 3:
        gpio.output(pin_enZ2, 0)
    else:
        gpio.output(pin_enZ2, 1)  
        
        
wasPoint = False        # true after a point drawing
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    
    mask = 0
    # check if this is the first light gun pulse
    if not wasGunPulse1 and gpio.input(pin_isGun1) == 0:
        mask = 1
        wasGunPulse1 = True
    if not wasGunPulse2 and gpio.input(pin_isGun2) == 0:
        mask = mask | 2
        wasGunPulse2 = True
        
    if mask != 0:
        return mask
    
    # print(gpio.input(pin_isGun1on), gpio.input(pin_isGun2on))
    # debounce switch 1 
    if gpio.input(pin_isGun1on) == 0:
        # while switch is on, restart timer
        gunTime1 = time.time()
    else:
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            wasGunPulse1 = False
            
    # debounce switch 2
    if gpio.input(pin_isGun2on) == 0:
        # while switch is on, restart timer
        gunTime2 = time.time()
    else:
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    Note that setKeys() can virtually set a key
    """
    res = 0 
    if gpio.input(pin_isKey) == 0:
        res = 1
    if gpio.input(pin_LED1) == 0:
        res += 2
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    # use global variables for gpio and spi
    # initialize
    gpio.setmode(gpio.BCM)
    gpio.setup(pin_doMove, gpio.OUT)
    gpio.output(pin_doMove, 0)
    gpio.setup(pin_doDraw, gpio.OUT)
    gpio.output(pin_doDraw, 0)
    gpio.setup(pin_isKey, gpio.IN, pull_up_down=gpio.PUD_UP)
    gpio.setup(pin_isGun1, gpio.IN, pull_up_down=gpio.PUD_UP)
    gpio.setup(pin_isGun2, gpio.IN, pull_up_down=gpio.PUD_UP)
    gpio.setup(pin_isGun1on, gpio.IN, pull_up_down=gpio.PUD_UP)
    gpio.setup(pin_isGun2on, gpio.IN, pull_up_down=gpio.PUD_UP)
    gpio.setup(pin_enZ1, gpio.OUT)
    gpio.setup(pin_enZ2, gpio.OUT)
    #  initially enable both
    gpio.output(pin_enZ1, 0)  # inverted: 0 is enable, 1 is disable
    gpio.output(pin_enZ2, 0)
    # set all LED / KEY pins pullup high so that the LED are free (off)
    gpio.setup(pin_LED1, gpio.IN, pull_up_down=gpio.PUD_UP)
    gpio.setup(pin_LED2, gpio.IN, pull_up_down=gpio.PUD_UP)
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
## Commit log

2023-07-17 initially
2023-07-19 Trigger switch with CMOS
2023-07-21 removed trigger switch hardware
2023-07-21 buges fixed
2023-07-21 Schematics as pdf added
2023-07-22 new one-shot light-gun
2023-07-22 light gun one-shot tested ok
2023-07-22 Updated schematics pdf
2023-07-24 cleanup
2023-07-24 chain of vectors for character and circle
2023-07-25 time.sleep has 70us overhead, use own
2023-07-25 long vector per segments
2023-07-25 minor changes
2023-07-26 Update ReadMe.md: adding link to GF's simulator
2023-08-07 Added list of scopes in ReadME
2023-08-14 Added lightgun for OPL-820
2023-08-26 before 1.0
2023-08-27 Schematics for 1.0a
2023-08-29 1.0c: moved I²C to own bus
2023-09-01 KiCad: EDA updates for PCB production; preliminary tap and switches; ReadMe.md updated
2023-09-02 revise tap board
2023-09-02 Enlarge board, larger PB
2023-09-02 correct tap board pictures
2023-09-03 vecIFbase created, OXO game for 2 players basic functions moved to vecIFbase.py module from vecIF.py OXO (tic-tac-toe) programmed in python for two playerse
2023-09-08 Cut 3.3 / VccDAC for Arduino test
2023-09-08 lightgun lamp
2023-09-13 Update lightgun LED, add HV, fixes
2023-09-18 key get and set, selection of programmes
2023-09-20 small fixes
2023-09-26 small corrections
2023-09-27 added TWS to select.sh
2023-10-07 unify with my version of the simulator
2023-10-07 kicad fixes
2023-10-09 ignore setting key 0
2023-10-09 debug mode in select
2023-10-09 Update ReadMe.md (fixed URL)
2023-10-10 button handling in vecIF
2023-10-10 enhancements (circle, character, delay) The check circle now points also the circle points to check the accuracy.
    Move delay back to 35µs
    Extra move at charcter start (effectively just an extra delay)
2023-10-11 Fixes in Schematics
2024-02-12 Update select.sh
    added one comment on line 2
2024-02-12 Revert "Update select.sh"
    This reverts commit 6b5dd59ec86c36e9a9bc551123a2aae5cd7ef73f.
    local changes were newer, spoiled by pull
2024-02-12 add more examples, more distance of selection point
2024-02-12 removed duplicate select.sh
2024-02-13 New directory with tests or examples in WW code
2024-08-12 Some minor changes
2024-08-12 Library of used footprints
2024-08-12 Add missing fp-lib-table to have Library.pretty added locally.
2024-08-12 local library for extra symbols
2024-08-12 Fix symbol reference to local library
2024-08-15 Templates relative local
2024-08-15 Remove Leybold Amplifier (should not be here)
